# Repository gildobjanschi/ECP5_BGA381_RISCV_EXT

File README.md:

# Extension board for ECP5_BGA381_RISCV
This is an extension board for the [ECP5_BGA381_RISCV](https://github.com/gildobjanschi/ECP5_BGA381_RISCV) board. To me it was very useful in monitoring processor is operations in terms of reading/writting registers, ROM, RAM, IO, knowing that interrupts occur, visualizing the instruction execution pipeline, cache hits and what instruction is generating a trap.

## How To setup KiCAD
Checkout the KiCAD project and open it. In the Configure Paths dialog add: Name: ECP5_BGA381_RISCV_EXT and Path: "The full path to the GitHub directory"/GitHub/ECP5_BGA381_RISCV_EXT

In the Manage Footprint Libraries click the Project Specific Libraries tab and add: Name: ECP5_BGA381_RISCV_EXT and Library Path: ${ECP5_BGA381_RISCV_EXT}/footprints/Footprints.kicad_sym

## Project Status
The board has been manufactured and it is fully verified.

[Schematic](https://github.com/gildobjanschi/ECP5_BGA381_RISCV_EXT/blob/main/kicad/ECP5_ext.pdf)

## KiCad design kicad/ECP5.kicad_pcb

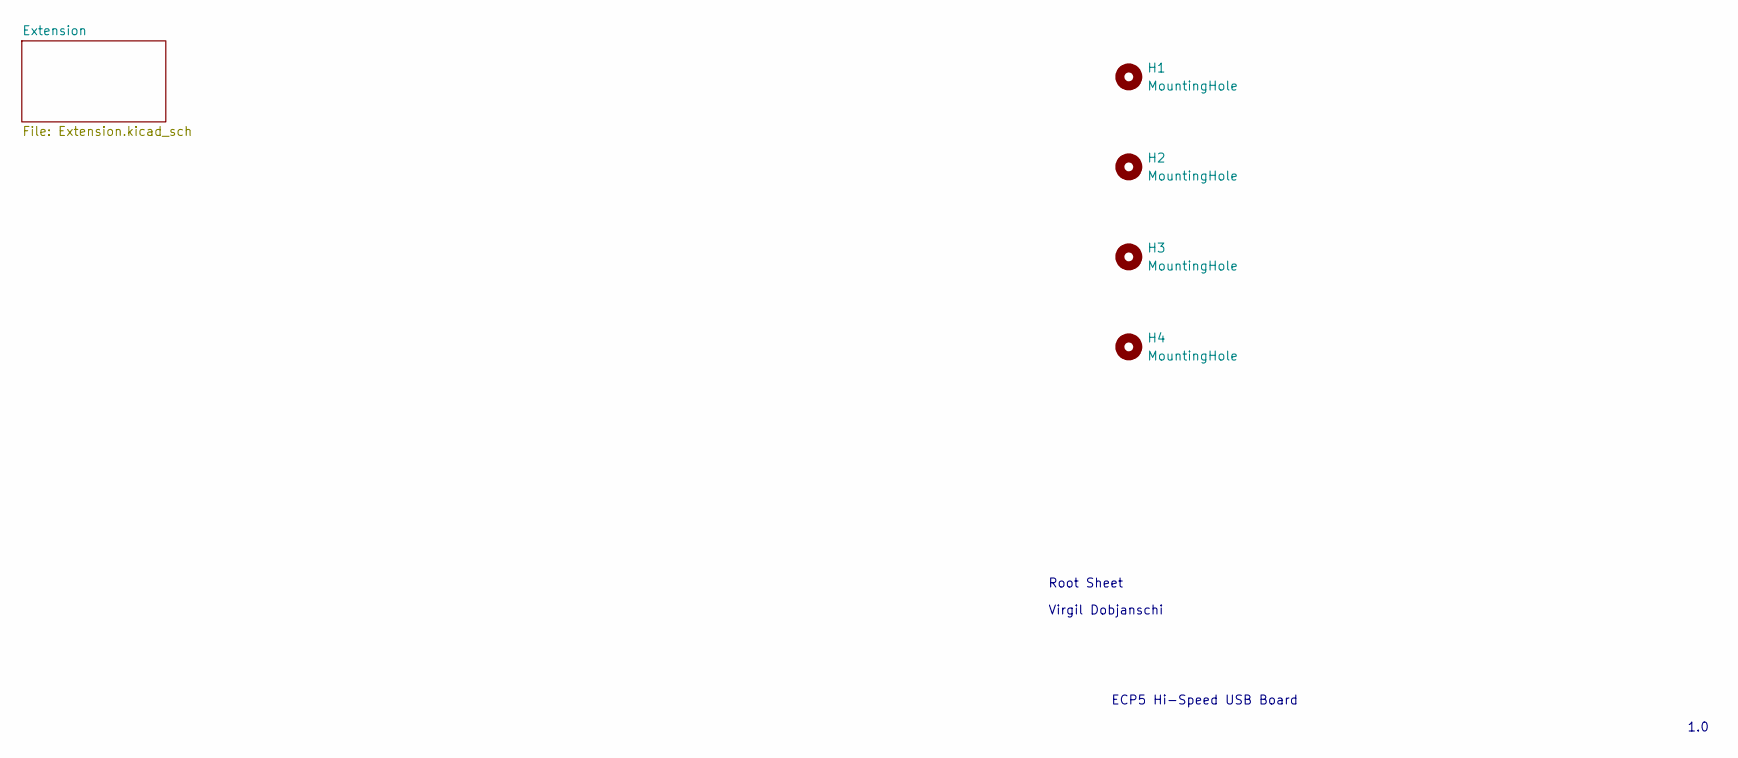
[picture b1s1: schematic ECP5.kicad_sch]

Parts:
H1, H2, H3, H4: MountingHole; MountingHole_3.2mm_M3

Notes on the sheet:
ECP5 Hi-Speed USB Board
Root Sheet
Virgil Dobjanschi
1.0

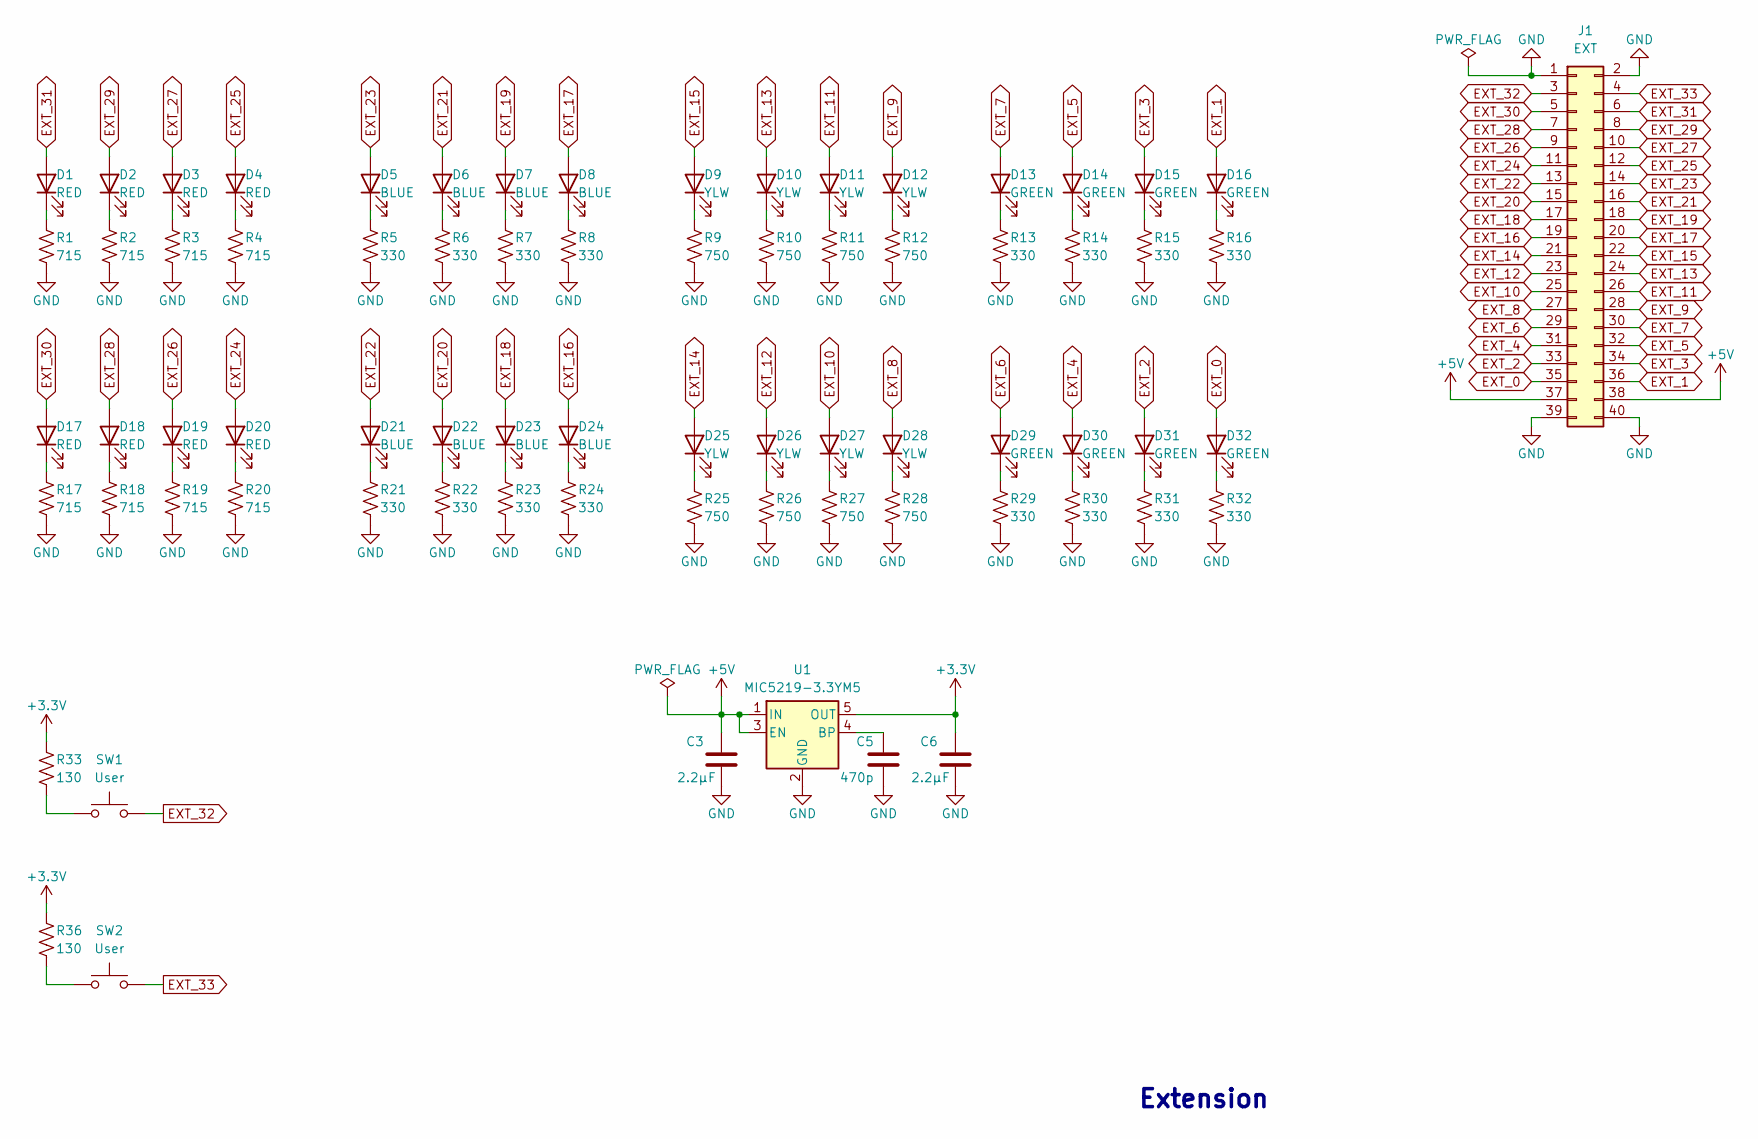
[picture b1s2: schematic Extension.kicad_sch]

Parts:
C3, C6: 2.2µF; C_1206_3216Metric; MPN TPSA225K010T1800
C5: 470p; C_0603_1608Metric; MPN 885012006042
D1, D2, D3, D4, D17, D18, D19, D20: RED; LED_0603_1608Metric; MPN APTD1608LSURCK
D5, D6, D7, D8, D21, D22, D23, D24: BLUE; LED_0603_1608Metric; MPN APTD1608LVBC/D
D9, D10, D11, D12, D25, D26, D27, D28: YLW; LED_0603_1608Metric; MPN APTD1608LSYCK/J3-PF
D13, D14, D15, D16, D29, D30, D31, D32: GREEN; LED_0603_1608Metric; MPN APTD1608LZGCK
J1: EXT; SAMTEC_FLE-120-01-G-DV-A; MPN FLE-120-01-G-DV-A-P-TR
R1, R2, R3, R4, R17, R18, R19, R20: 715; R_0603_1608Metric; MPN ERJ-3EKF7150V
R5, R6, R7, R8, R13, R14, R15, R16, R21, R22, R23, R24, R29, R30, R31, R32: 330; R_0603_1608Metric; MPN ERJ-3EKF3300V
R9, R10, R11, R12, R25, R26, R27, R28: 750; R_0603_1608Metric; MPN ERJ-3EKF7500V
R33, R36: 130; R_0603_1608Metric; MPN ERJ-3EKF1300V
SW1, SW2: User; SW_SPST_PTS645; MPN PTS645SM43SMTR92 LFS
U1: MIC5219-3.3YM5; SOT-23-5; MPN MIC5219-3.3YM5-TR

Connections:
EXT_0: D32.2 (A), J1.35
EXT_1: D16.2 (A), J1.36
EXT_2: D31.2 (A), J1.33
EXT_3: D15.2 (A), J1.34
EXT_4: D30.2 (A), J1.31
EXT_5: D14.2 (A), J1.32
EXT_6: D29.2 (A), J1.29
EXT_7: D13.2 (A), J1.30
EXT_8: D28.2 (A), J1.27
EXT_9: D12.2 (A), J1.28
EXT_10: D27.2 (A), J1.25
EXT_11: D11.2 (A), J1.26
EXT_12: D26.2 (A), J1.23
EXT_13: D10.2 (A), J1.24
EXT_14: D25.2 (A), J1.21
EXT_15: D9.2 (A), J1.22
EXT_16: D24.2 (A), J1.19
EXT_17: D8.2 (A), J1.20
EXT_18: D23.2 (A), J1.17
EXT_19: D7.2 (A), J1.18
EXT_20: D22.2 (A), J1.15
EXT_21: D6.2 (A), J1.16
EXT_22: D21.2 (A), J1.13
EXT_23: D5.2 (A), J1.14
EXT_24: D20.2 (A), J1.11
EXT_25: D4.2 (A), J1.12
EXT_26: D19.2 (A), J1.9
EXT_27: D3.2 (A), J1.10
EXT_28: D18.2 (A), J1.7
EXT_29: D2.2 (A), J1.8
EXT_30: D17.2 (A), J1.5
EXT_31: D1.2 (A), J1.6
EXT_32: J1.3, SW1.2
EXT_33: J1.4, SW2.2
GND: C6.2, J1.1, J1.2, J1.39, J1.40, R1.2, R2.2, R3.2, R4.2, R5.2, R6.2, R7.2, R8.2, R9.2, R10.2, R11.2, R12.2, R13.2, R14.2, R15.2, R16.2, R17.2, R18.2, R19.2, R20.2, R21.2, R22.2, R23.2, R24.2, R25.2, R26.2, R27.2, R28.2, R29.2, R30.2, R31.2, R32.2; also elsewhere on the board
unnamed: D1.1 (K), R1.1
unnamed: D2.1 (K), R2.1
unnamed: D3.1 (K), R3.1
unnamed: D4.1 (K), R4.1
unnamed: D5.1 (K), R5.1
unnamed: D6.1 (K), R6.1
unnamed: D7.1 (K), R7.1
unnamed: D8.1 (K), R8.1
unnamed: D9.1 (K), R9.1
unnamed: D10.1 (K), R10.1
unnamed: D11.1 (K), R11.1
unnamed: D12.1 (K), R12.1
unnamed: D13.1 (K), R13.1
unnamed: D14.1 (K), R14.1
unnamed: D15.1 (K), R15.1
unnamed: D16.1 (K), R16.1
unnamed: D17.1 (K), R17.1
unnamed: D18.1 (K), R18.1
unnamed: D19.1 (K), R19.1
unnamed: D20.1 (K), R20.1
unnamed: D21.1 (K), R21.1
unnamed: D22.1 (K), R22.1
unnamed: D23.1 (K), R23.1
unnamed: D24.1 (K), R24.1
unnamed: D25.1 (K), R25.1
unnamed: D26.1 (K), R26.1
unnamed: D27.1 (K), R27.1
unnamed: D28.1 (K), R28.1
unnamed: D29.1 (K), R29.1
unnamed: D30.1 (K), R30.1
unnamed: D31.1 (K), R31.1
unnamed: D32.1 (K), R32.1
unnamed: R33.2, SW1.1
unnamed: R36.2, SW2.1

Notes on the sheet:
Extension

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
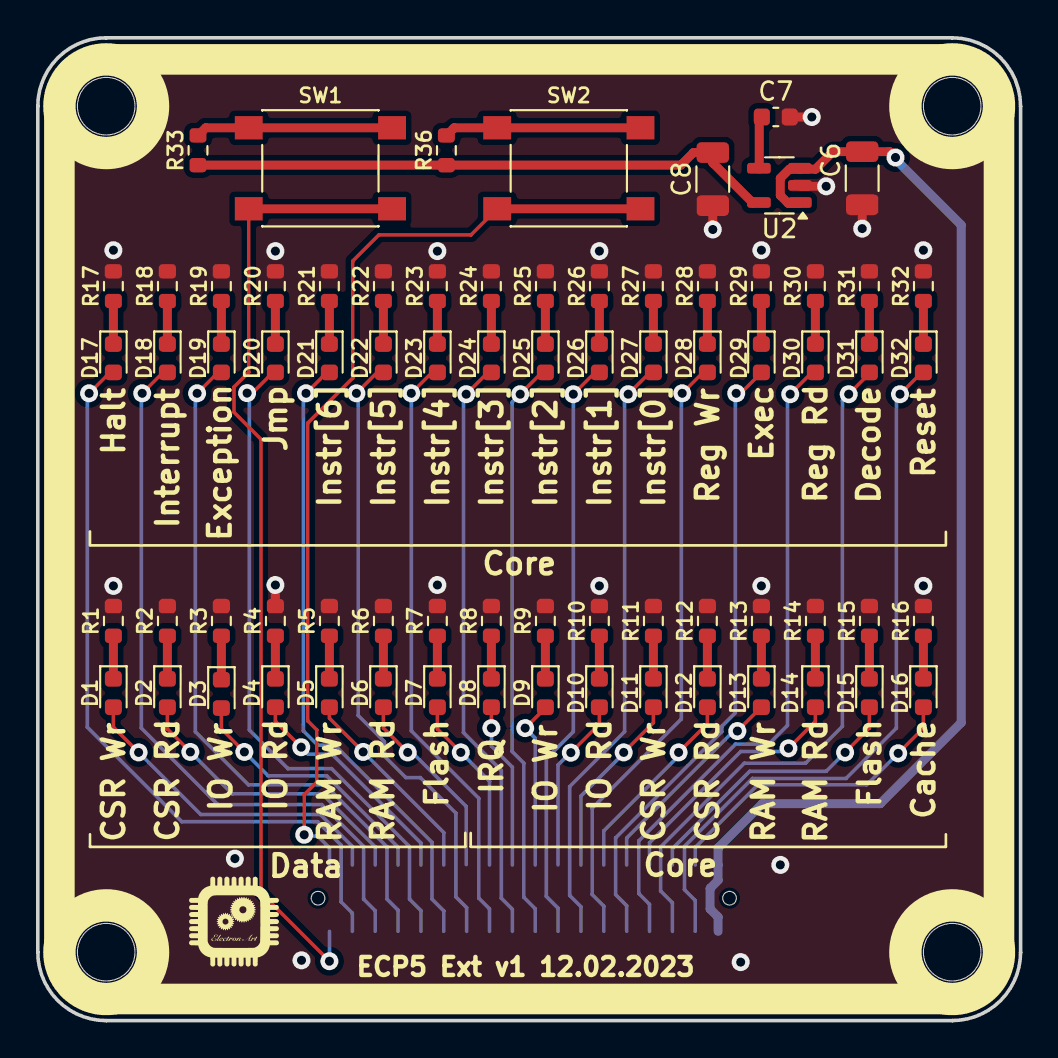
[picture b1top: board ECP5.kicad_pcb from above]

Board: 4 copper layers, 54.6 x 54.6 mm, 77 parts (1 on the bottom side), 72 nets.

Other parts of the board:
C7: 470p; C_0603_1608Metric
C8: 2.2µF; C_1206_3216Metric
U2: MIC5219-3.3YM5; SOT-23-5

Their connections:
GND: C7.2, C8.2, U2.2 (GND); also elsewhere on the board
unnamed: C7.1, U2.4 (BP)

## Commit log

2024-09-06 First checkin
2024-09-06 Added 3D view
2024-09-06 Added schematic PDF
